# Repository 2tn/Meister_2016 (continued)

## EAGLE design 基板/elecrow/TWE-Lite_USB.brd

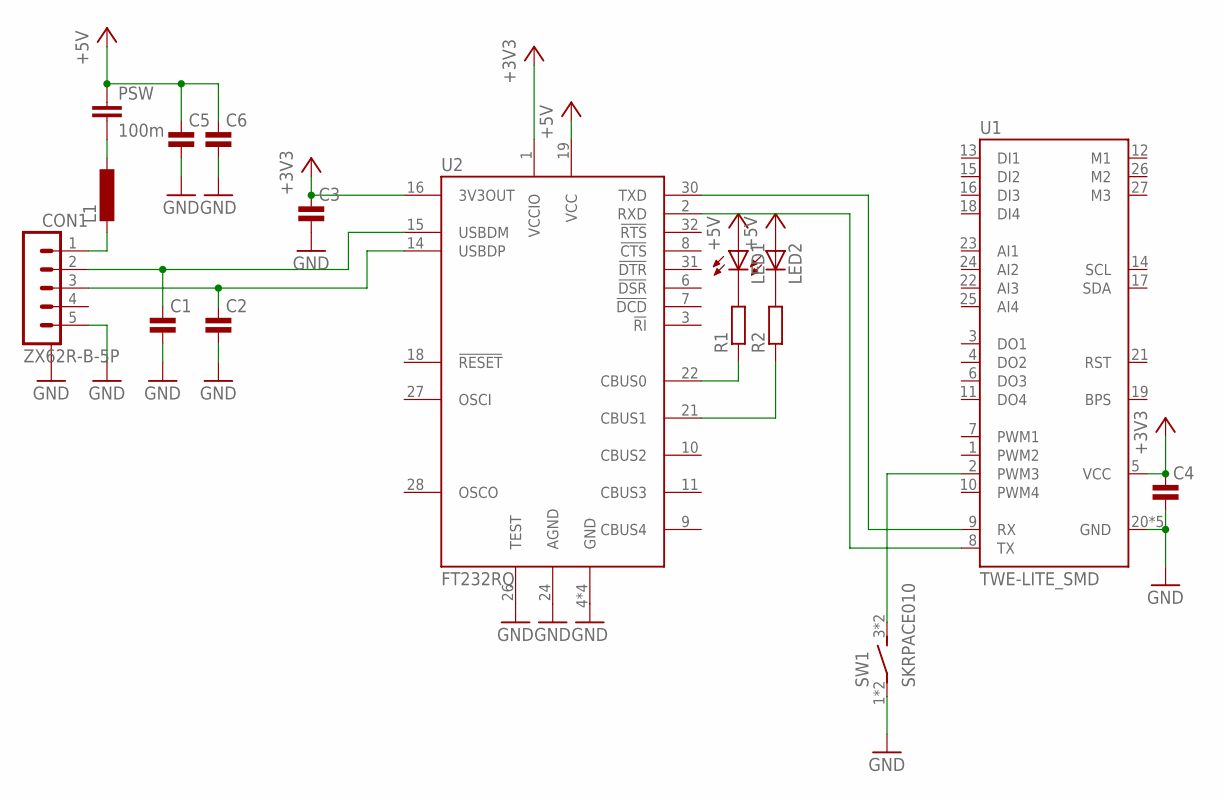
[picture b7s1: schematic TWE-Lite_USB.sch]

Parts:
C1, C2, C3, C4, C5, C6: C0402; 0402
CON1: ZX62R-B-5P; MICRO-B
L1: L-EU; C0603K
LED1, LED2: LEDSML0603; SML0603
PSW: 100m; C3225
R1, R2: R-EU_R0402; R0402
SW1: SKRPACE010
U1: TWE-LITE_SMD; LITE
U2: FT232RQ; QFN32

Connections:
+3V3: C3.1, C4.1, U1.5 (VCC), U2.1 (VCCIO), U2.16 (3V3OUT)
+5V: C5.1, C6.1, LED1.A, LED2.A, PSW.1, U2.19 (VCC)
GND: C1.2, C2.2, C3.2, C4.2, C5.2, C6.2, CON1.5 (1.VBUS), CON1.CASE@1, CON1.CASE@2, CON1.CASE@3, CON1.CASE@4, SW1.1, SW1.2, U1.20 (GND), U1.28 (GND), U1.30 (GND), U1.31 (GND), U1.32 (GND), U2.4 (GND), U2.17 (GND), U2.20 (GND), U2.24 (AGND), U2.26 (TEST), U2.PAD (GND)
unnamed: C1.1, CON1.2 (4.ID), U2.15 (USBDM)
unnamed: C2.1, CON1.3 (3.D+), U2.14 (USBDP)
unnamed: CON1.1 (5.GND), L1.2
unnamed: LED1.C, R1.2
unnamed: U1.9 (RX), U2.30 (TXD)
unnamed: U1.8 (TX), U2.2 (RXD)
unnamed: SW1.3 (S), SW1.4 (S), U1.2 (PWM3)
unnamed: L1.1, PSW.2
unnamed: LED2.C, R2.2
unnamed: R1.1, U2.22 (CBUS0)
unnamed: R2.1, U2.21 (CBUS1)

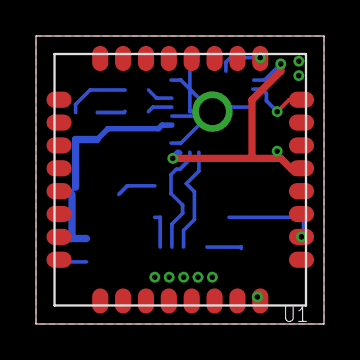
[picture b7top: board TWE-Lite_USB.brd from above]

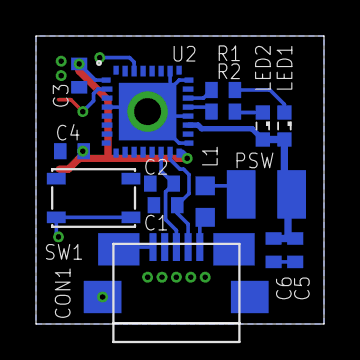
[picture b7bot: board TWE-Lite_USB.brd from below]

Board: 2 copper layers, 16.0 x 16.0 mm, 16 parts (15 on the bottom side), 14 nets.

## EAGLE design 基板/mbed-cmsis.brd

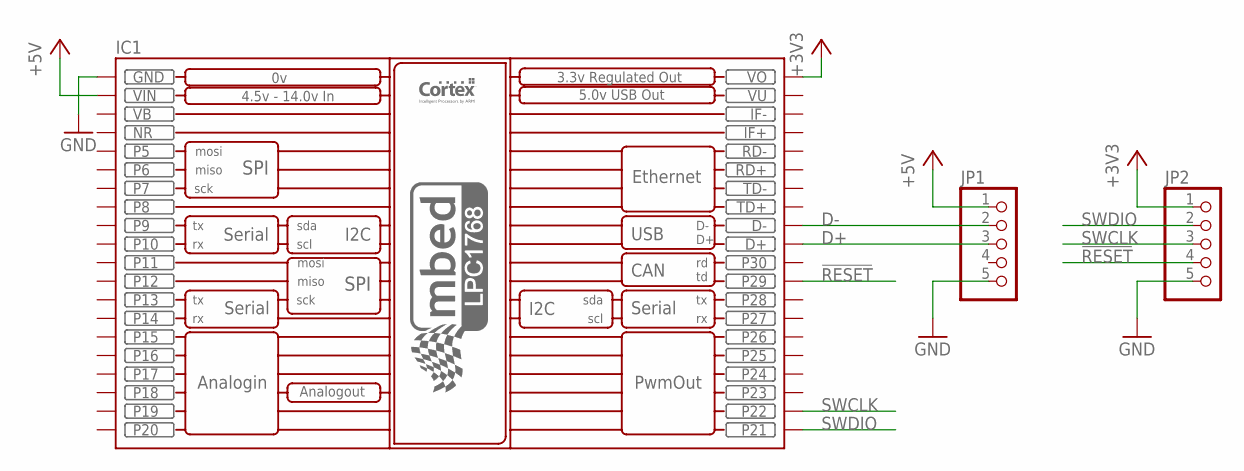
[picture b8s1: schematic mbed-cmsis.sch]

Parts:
IC1: MBED_NXP_LPC1768; MBED-KIT
JP1, JP2: PINHD-1X5; 1X05

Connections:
!RESET!: IC1.P$29 (P29), JP2.4
+3V3: IC1.VOUT (VO), JP2.1
+5V: IC1.VIN, JP1.1
D+: IC1.D+, JP1.3
D-: IC1.D-, JP1.2
GND: IC1.GND, JP1.5, JP2.5
NR: IC1.NR
SWCLK: IC1.P$22 (P22), JP2.3
SWDIO: IC1.P$21 (P21), JP2.2
VB: IC1.VB
VU: IC1.VU

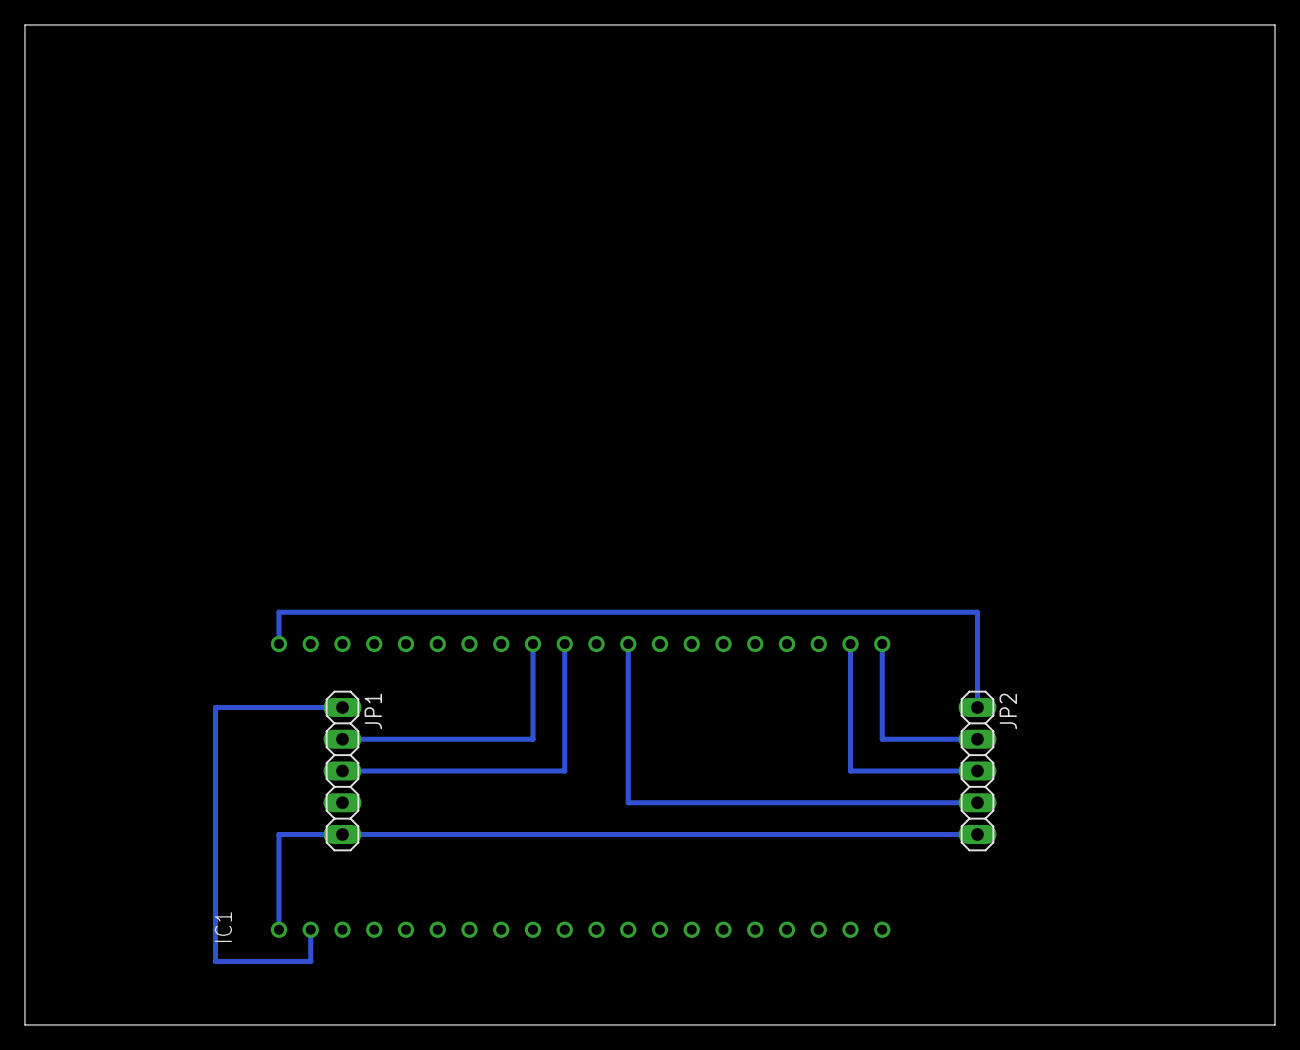
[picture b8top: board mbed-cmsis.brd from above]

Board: 2 copper layers, 100.0 x 80.0 mm, 3 parts (0 on the bottom side), 8 nets.

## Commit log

2018-05-12 androidプログラム追加
